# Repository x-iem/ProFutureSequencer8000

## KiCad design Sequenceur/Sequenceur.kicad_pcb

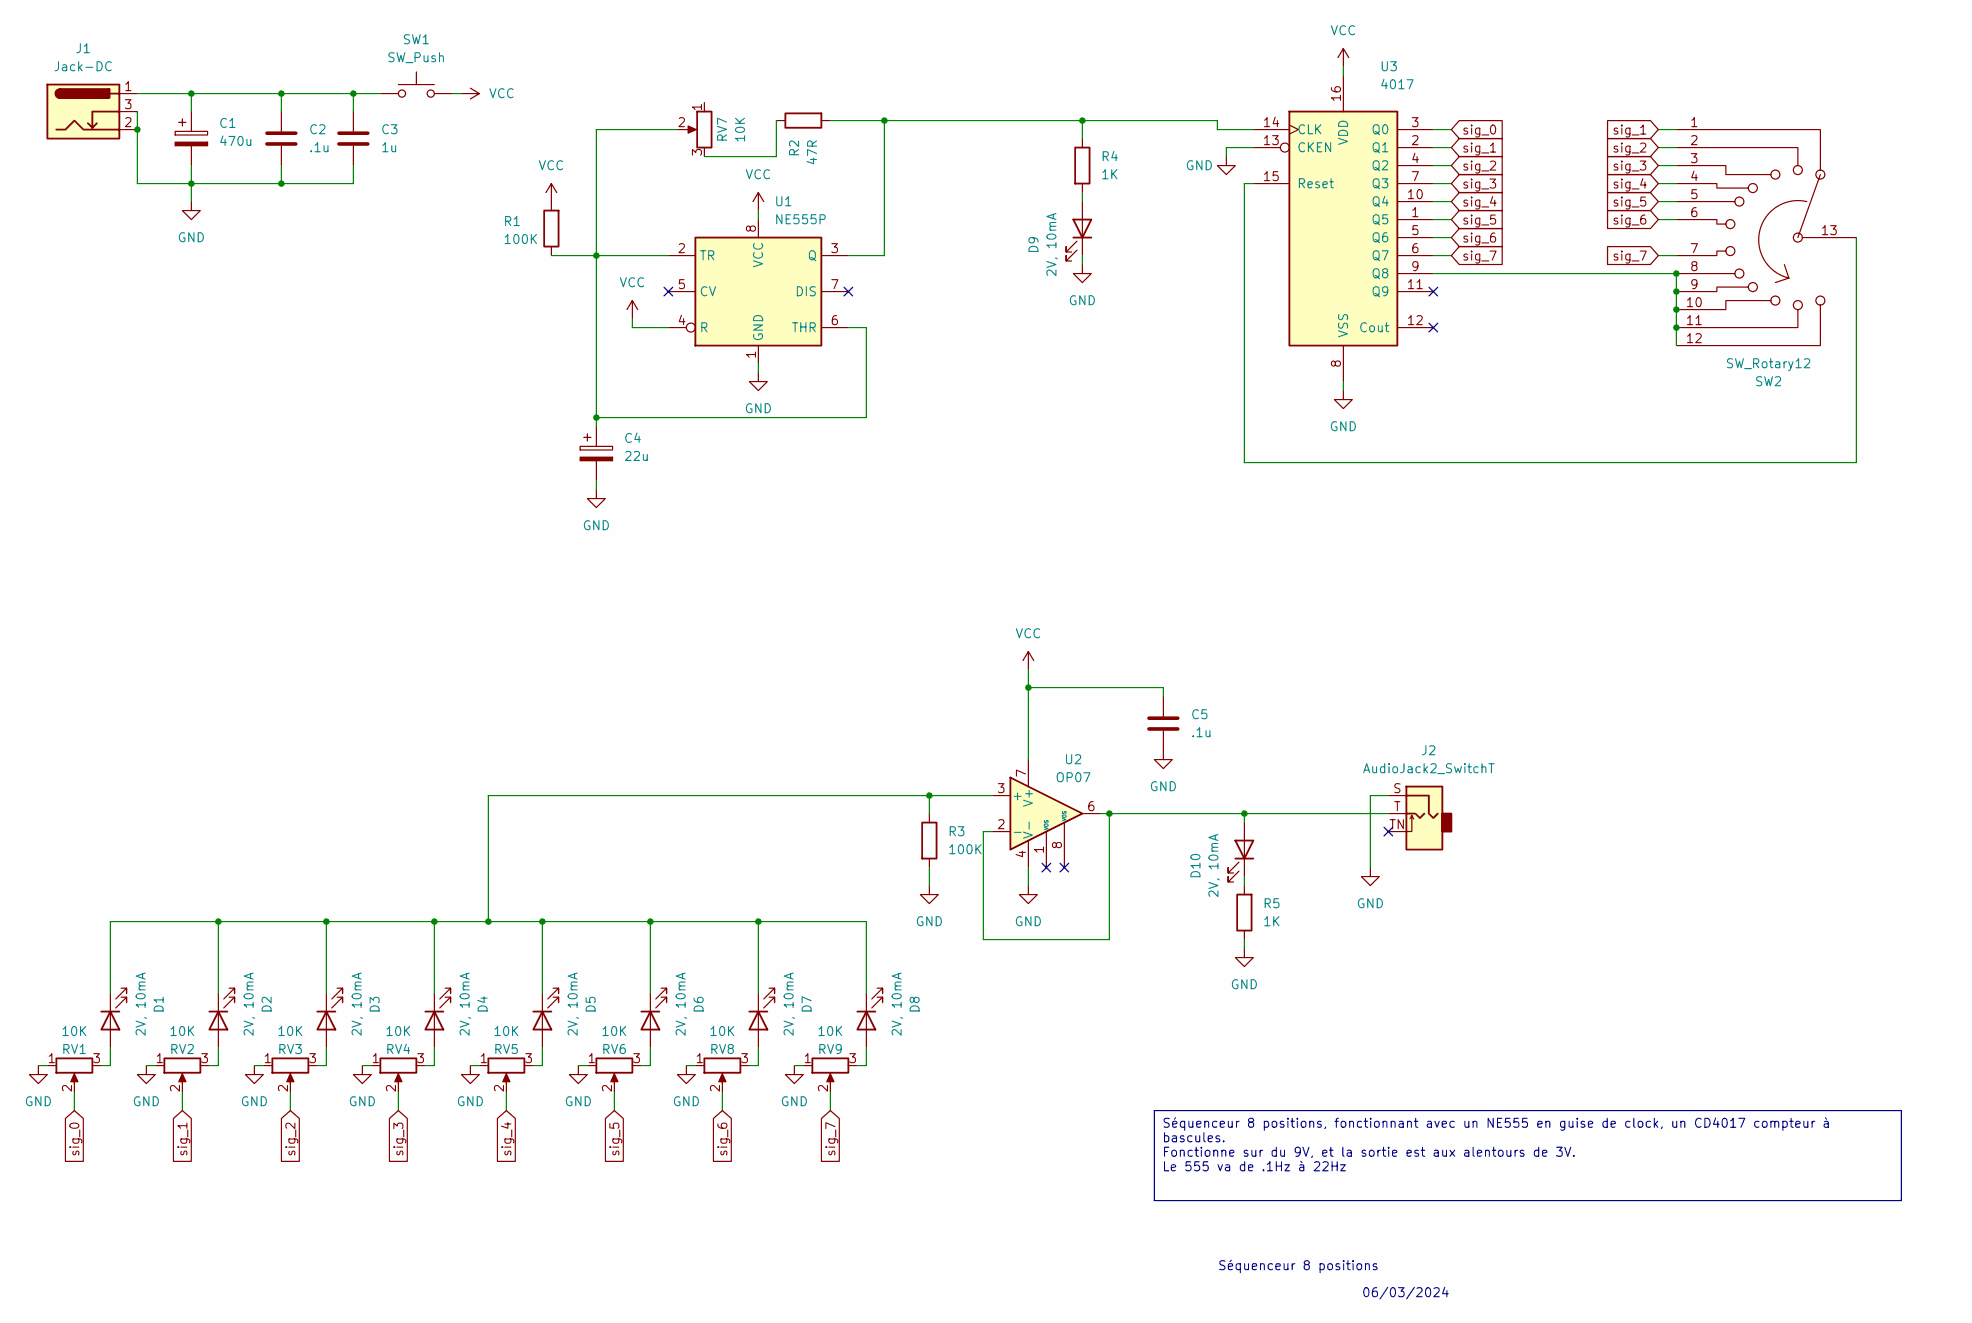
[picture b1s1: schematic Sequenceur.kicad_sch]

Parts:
C1: 470u; CP_Radial_D5.0mm_P2.50mm
C2, C5: .1u; C_0805_2012Metric
C3: 1u; C_0805_2012Metric
C4: 22u; CP_Radial_D5.0mm_P2.50mm
D1, D2, D3, D4, D5, D6, D7, D8, D9, D10: 2V, 10mA; LED_D5.0mm
J1: Jack-DC; BarrelJack_Horizontal
J2: AudioJack2_SwitchT; Jack_6.35_TTnS
R1, R3: 100K; R_0603_1608Metric
R2: 47R; R_0805_2012Metric
R4, R5: 1K; R_0603_1608Metric
RV1, RV2, RV3, RV4, RV5, RV6, RV7, RV8, RV9: 10K; POTENTIOMETER_BOARDMNT_VERTICAL
SW1: SW_Push; Switch_2pin
SW2: SW_Rotary12; MC00L1NCQD
U1: NE555P; DIP-8_W7.62mm
U2: OP07; DIP-8
U3: 4017; CD4017BM

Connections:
GND: C1.2, C2.2, C3.2, C4.2, C5.2, D9.1 (K), J1.2, J1.3, J2.S, R3.2, R5.1, RV1.1, RV2.1, RV3.1, RV4.1, RV5.1, RV6.1, RV8.1, RV9.1, U1.1 (GND), U2.4 (V-), U3.8 (VSS), U3.13 (CKEN)
unnamed: C1.1, C2.1, C3.1, J1.1, SW1.1
unnamed: D1.2 (A), RV1.3
unnamed: D1.1 (K), D2.1 (K), D3.1 (K), D4.1 (K), D5.1 (K), D6.1 (K), D7.1 (K), D8.1 (K), R3.1, U2.3 (+)
unnamed: D2.2 (A), RV2.3
unnamed: D3.2 (A), RV3.3
unnamed: D4.2 (A), RV4.3
unnamed: D5.2 (A), RV5.3
unnamed: D6.2 (A), RV6.3
unnamed: D7.2 (A), RV8.3
unnamed: D8.2 (A), RV9.3
unnamed: D9.2 (A), R4.2
unnamed: D10.2 (A), J2.T, U2.2 (-), U2.6
unnamed: D10.1 (K), R5.2
unnamed: R2.1, RV7.3
unnamed: R2.2, R4.1, U1.3 (Q), U3.14 (CLK)
unnamed: C4.1, R1.1, RV7.2, U1.2 (TR), U1.6 (THR)
unnamed: SW2.8, SW2.9, SW2.10, SW2.11, SW2.12, U3.9 (Q8)
unnamed: SW2.13, U3.15 (Reset)
VCC: C5.1, R1.2, SW1.2, U1.4 (R), U1.8 (VCC), U2.7 (V+), U3.16 (VDD)
sig_0: RV1.2, U3.3 (Q0)
sig_1: RV2.2, SW2.1, U3.2 (Q1)
sig_2: RV3.2, SW2.2, U3.4 (Q2)
sig_3: RV4.2, SW2.3, U3.7 (Q3)
sig_4: RV5.2, SW2.4, U3.10 (Q4)
sig_5: RV6.2, SW2.5, U3.1 (Q5)
sig_6: RV8.2, SW2.6, U3.5 (Q6)
sig_7: RV9.2, SW2.7, U3.6 (Q7)

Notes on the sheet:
Séquenceur 8 positions, fonctionnant avec un NE555 en guise de clock, un CD4017 compteur à bascules. Fonctionne sur du 9V, et la sortie est aux alentours de 3V. Le 555 va de .1Hz à 22Hz
06/03/2024
Séquenceur 8 positions

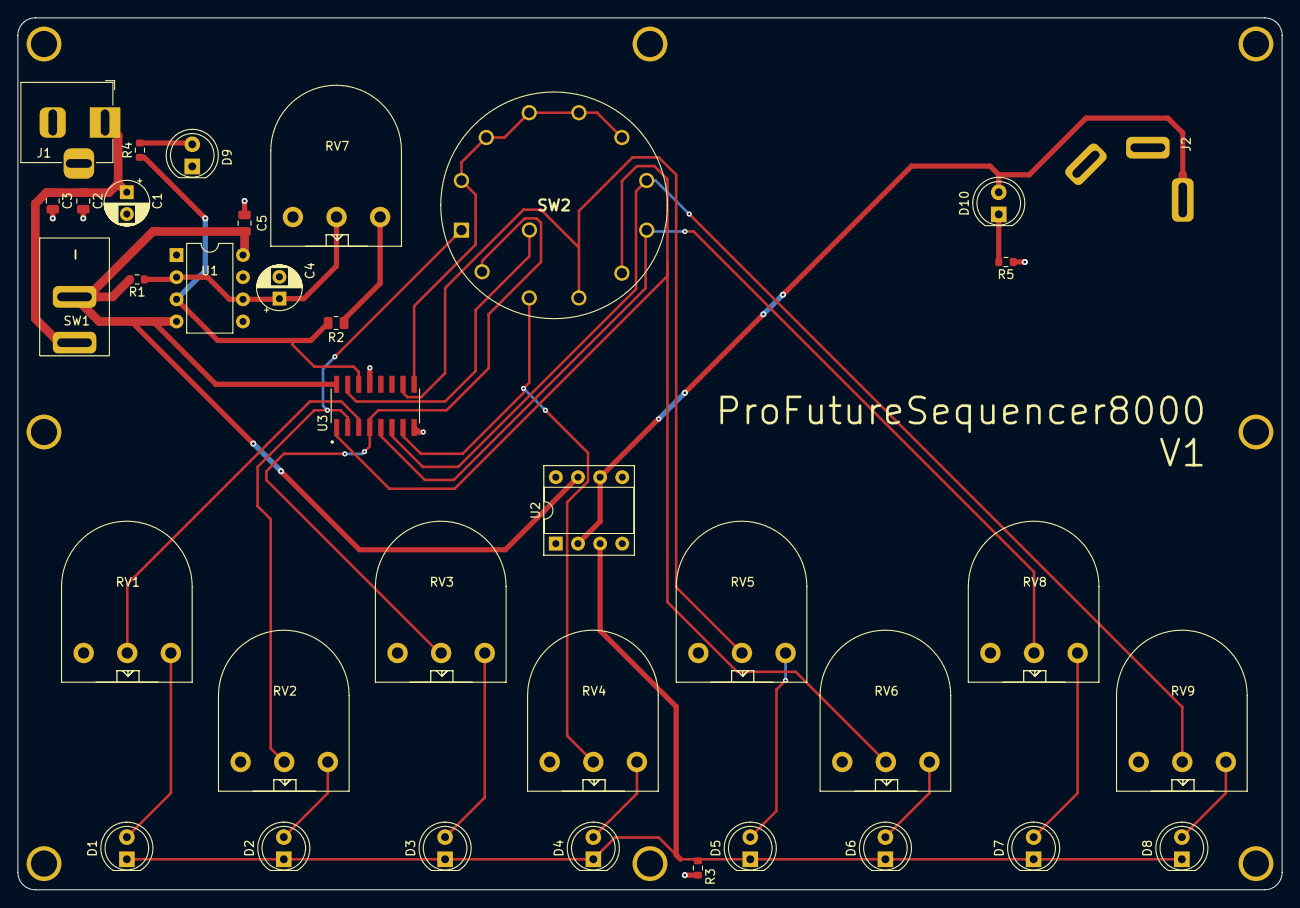
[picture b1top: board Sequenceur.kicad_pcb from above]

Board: 2 copper layers, 145.0 x 100.0 mm, 36 parts (0 on the bottom side), 28 nets.

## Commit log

2024-06-06 Modified schematic to enable 50% theoretical duty cycle.
2024-06-17 First real version of the PCB, as a 2 layer one, and with adapted footprints.
